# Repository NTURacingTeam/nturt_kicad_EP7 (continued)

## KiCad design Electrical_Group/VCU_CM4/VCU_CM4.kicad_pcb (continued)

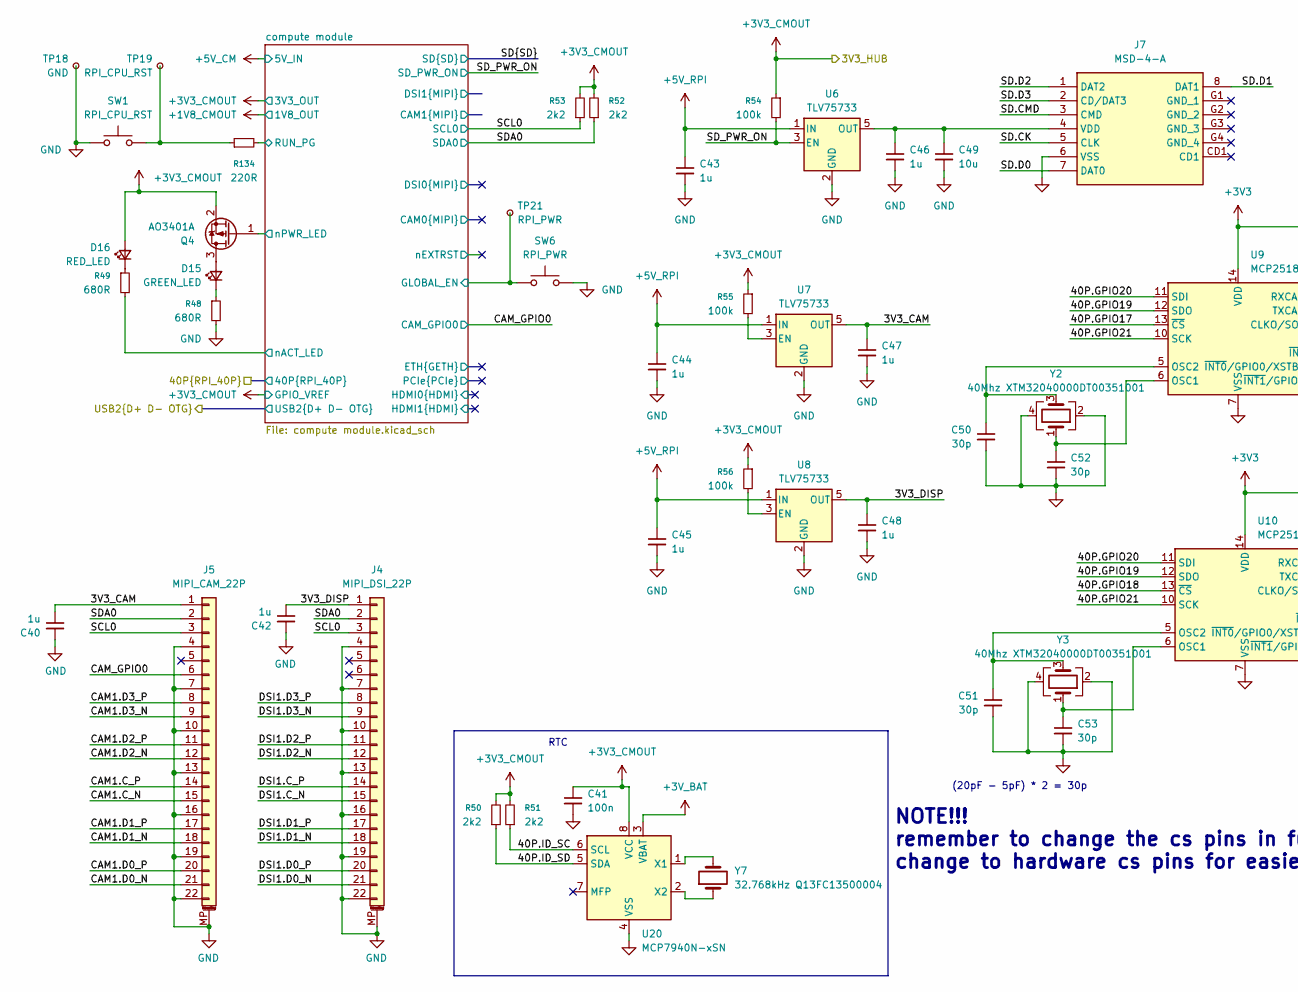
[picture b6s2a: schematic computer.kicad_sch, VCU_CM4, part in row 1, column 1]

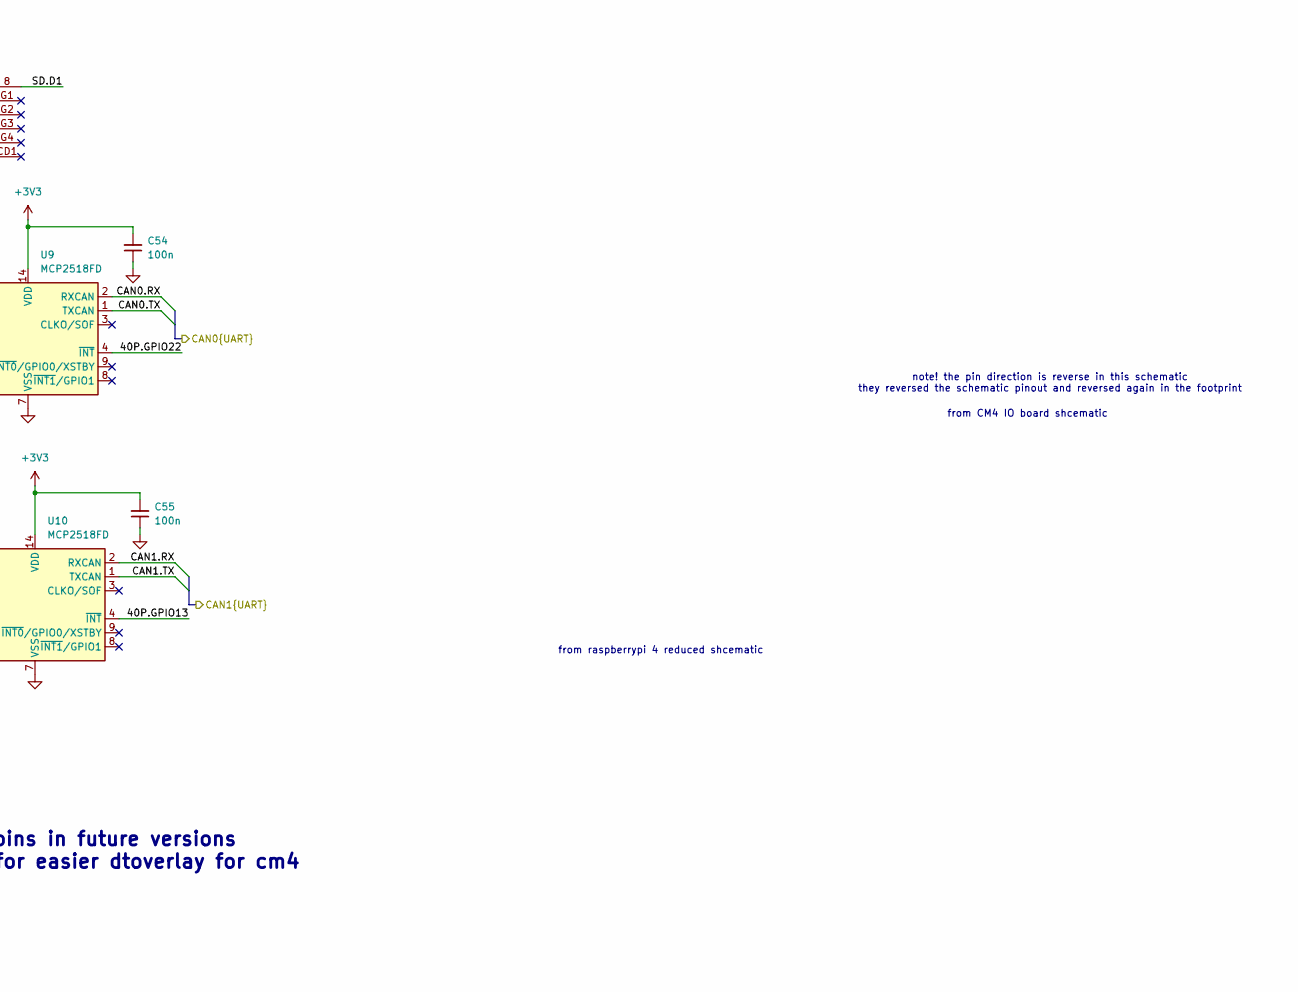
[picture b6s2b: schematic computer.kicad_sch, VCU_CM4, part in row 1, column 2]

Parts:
C40, C42, C43, C44, C45, C46, C47, C48: 1u; C_0402_1005Metric
C41: 100n; C_0603_1608Metric
C49: 10u; C_0603_1608Metric
C50, C51, C52, C53: 30p; C_0402_1005Metric
C54, C55: 100n; C_0402_1005Metric
D15: GREEN_LED; LED_0603_1608Metric
D16: RED_LED; LED_0603_1608Metric
J4: MIPI_DSI_22P; Hirose_FH12-22S-0.5SH_1x22-1MP_P0.50mm_Horizontal; Part Description 22 Position FFC, FPC Connector Contacts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
J5: MIPI_CAM_22P; Hirose_FH12-22S-0.5SH_1x22-1MP_P0.50mm_Horizontal; Part Description 22 Position FFC, FPC Connector Contacts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
J7: MSD-4-A; MSD4A; Mouser Part Number 179-MSD-4-A
Q4: AO3401A; SOT-23
R48, R49: 680R; R_0402_1005Metric
R50, R51, R52, R53: 2k2; R_0402_1005Metric
R54, R55, R56: 100k; R_0402_1005Metric
R134: 220R; R_0402_1005Metric
SW1: RPI_CPU_RST; SW_Tactile_SPST_NO_Straight_CK_PTS636Sx25SMTRLFS
SW6: RPI_PWR; SW_Tactile_SPST_NO_Straight_CK_PTS636Sx25SMTRLFS
TP18: GND; edge_pad_1.4mm_0.7mm
TP19: RPI_CPU_RST; edge_pad_1.4mm_0.7mm
TP21: RPI_PWR; edge_pad_1.4mm_0.7mm
U6, U7, U8: TLV75733; SOT-23-5
U9, U10: MCP2518FD; SOIC-14_3.9x8.7mm_P1.27mm
U20: MCP7940N-xSN; SOIC-8_3.9x4.9mm_P1.27mm
Y2, Y3: 40Mhz XTM32040000DT00351001; Crystal_SMD_3225-4Pin_3.2x2.5mm
Y7: 32.768kHz Q13FC13500004; Crystal_SMD_3215-2Pin_3.2x1.5mm

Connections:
+3V3: C54.2, C55.2, U9.14 (VDD), U10.14 (VDD); also elsewhere on the board
+3V3_CMOUT: C41.1, D16.2 (A), Q4.2 (S), R50.2, R51.2, R52.2, R53.2, R54.1, R55.1, R56.1, U20.8 (VCC); also elsewhere on the board
+3V_BAT: U20.3 (VBAT); also elsewhere on the board
+5V_CM: C43.1, C44.1, C45.1, U6.1 (IN), U7.1 (IN), U8.1 (IN); also elsewhere on the board
/RPI CAN0/CAN.RX: U9.2 (RXCAN); also elsewhere on the board
/RPI CAN0/CAN.TX: U9.1 (TXCAN); also elsewhere on the board
/RPI CAN1/CAN.RX: U10.2 (RXCAN); also elsewhere on the board
/RPI CAN1/CAN.TX: U10.1 (TXCAN); also elsewhere on the board
/computer/3V3_CAM: C40.1, C47.1, J5.1, U7.5 (OUT)
/computer/3V3_DISP: C42.1, C48.1, J4.1, U8.5 (OUT)
/computer/40P.GPIO13: U10.4 (~INT); also elsewhere on the board
/computer/40P.GPIO17: U9.13 (~CS); also elsewhere on the board
/computer/40P.GPIO18: U10.13 (~CS); also elsewhere on the board
/computer/40P.GPIO19: U9.12 (SDO), U10.12 (SDO); also elsewhere on the board
/computer/40P.GPIO20: U9.11 (SDI), U10.11 (SDI); also elsewhere on the board
/computer/40P.GPIO21: U9.10 (SCK), U10.10 (SCK); also elsewhere on the board
/computer/40P.GPIO22: U9.4 (~INT); also elsewhere on the board
/computer/40P.ID_SC: R51.1, U20.6 (SCL); also elsewhere on the board
/computer/40P.ID_SD: R50.1, U20.5 (SDA); also elsewhere on the board
/computer/CAM_GPIO0: J5.6; also elsewhere on the board
/computer/SCL0: J4.3, J5.3, R53.1; also elsewhere on the board
/computer/SD.CK: J7.5 (CLK); also elsewhere on the board
/computer/SD.CMD: J7.3 (CMD); also elsewhere on the board
/computer/SD.D0: J7.7 (DAT0); also elsewhere on the board
/computer/SD.D1: J7.8 (DAT1); also elsewhere on the board
/computer/SD.D2: J7.1 (DAT2); also elsewhere on the board
/computer/SD.D3: J7.2 (CD/DAT3); also elsewhere on the board
/computer/SDA0: J4.2, J5.2, R52.1; also elsewhere on the board
/computer/SD_PWR_ON: R54.2, U6.3 (EN); also elsewhere on the board
/computer/compute module/CAM1.C_N: J5.15; also elsewhere on the board
/computer/compute module/CAM1.C_P: J5.14; also elsewhere on the board
/computer/compute module/CAM1.D0_N: J5.21; also elsewhere on the board
/computer/compute module/CAM1.D0_P: J5.20; also elsewhere on the board
/computer/compute module/CAM1.D1_N: J5.18; also elsewhere on the board
/computer/compute module/CAM1.D1_P: J5.17; also elsewhere on the board
/computer/compute module/CAM1.D2_N: J5.12; also elsewhere on the board
/computer/compute module/CAM1.D2_P: J5.11; also elsewhere on the board
/computer/compute module/CAM1.D3_N: J5.9; also elsewhere on the board
/computer/compute module/CAM1.D3_P: J5.8; also elsewhere on the board
/computer/compute module/DSI1.C_N: J4.15; also elsewhere on the board
/computer/compute module/DSI1.C_P: J4.14; also elsewhere on the board
/computer/compute module/DSI1.D0_N: J4.21; also elsewhere on the board
/computer/compute module/DSI1.D0_P: J4.20; also elsewhere on the board
/computer/compute module/DSI1.D1_N: J4.18; also elsewhere on the board
/computer/compute module/DSI1.D1_P: J4.17; also elsewhere on the board
/computer/compute module/DSI1.D2_N: J4.12; also elsewhere on the board
/computer/compute module/DSI1.D2_P: J4.11; also elsewhere on the board
/computer/compute module/DSI1.D3_N: J4.9; also elsewhere on the board
/computer/compute module/DSI1.D3_P: J4.8; also elsewhere on the board
/computer/compute module/GLOBAL_EN: SW6.1, TP21.1; also elsewhere on the board
/computer/compute module/RUN_PG: R134.2; also elsewhere on the board
/computer/compute module/nACT_LED: R49.2; also elsewhere on the board
/computer/compute module/nPWR_LED: Q4.1 (G); also elsewhere on the board
GND: C40.2, C41.2, C42.2, C43.2, C44.2, C45.2, C46.2, C47.2, C48.2, C49.2, C50.2, C51.2, C52.2, C53.2, C54.1, C55.1, J4.4, J4.7, J4.10, J4.13, J4.16, J4.19, J4.22, J4.MP (MountPin), J5.4, J5.7, J5.10, J5.13, J5.16, J5.19, J5.22, J5.MP (MountPin), J7.6 (VSS), R48.2, SW1.2, SW6.2, TP18.1, U6.2 (GND), U7.2 (GND), U8.2 (GND), U9.7 (VSS), U10.7 (VSS), U20.4 (VSS), Y2.2, Y2.4, Y3.2, Y3.4; also elsewhere on the board
unnamed: D15.2 (A), Q4.3 (D)
unnamed: D15.1 (K), R48.1
unnamed: D16.1 (K), R49.1
unnamed: C46.1, C49.1, J7.4 (VDD), U6.5 (OUT)
unnamed: R134.1, SW1.1, TP19.1
unnamed: R55.2, U7.3 (EN)
unnamed: R56.2, U8.3 (EN)
unnamed: C52.1, U9.6 (OSC1), Y2.1
unnamed: C50.1, U9.5 (OSC2), Y2.3
unnamed: C53.1, U10.6 (OSC1), Y3.1
unnamed: C51.1, U10.5 (OSC2), Y3.3
unnamed: U20.1 (X1), Y7.2
unnamed: U20.2 (X2), Y7.1

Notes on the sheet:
from raspberrypi 4 reduced shcematic
note! the pin direction is reverse in this schematic they reversed the schematic pinout and reversed again in the footprint
(20pF - 5pF) * 2 = 30p
NOTE!!! remember to change the cs pins in future versions change to hardware cs pins for easier dtoverlay for cm4
from CM4 IO board shcematic
RTC

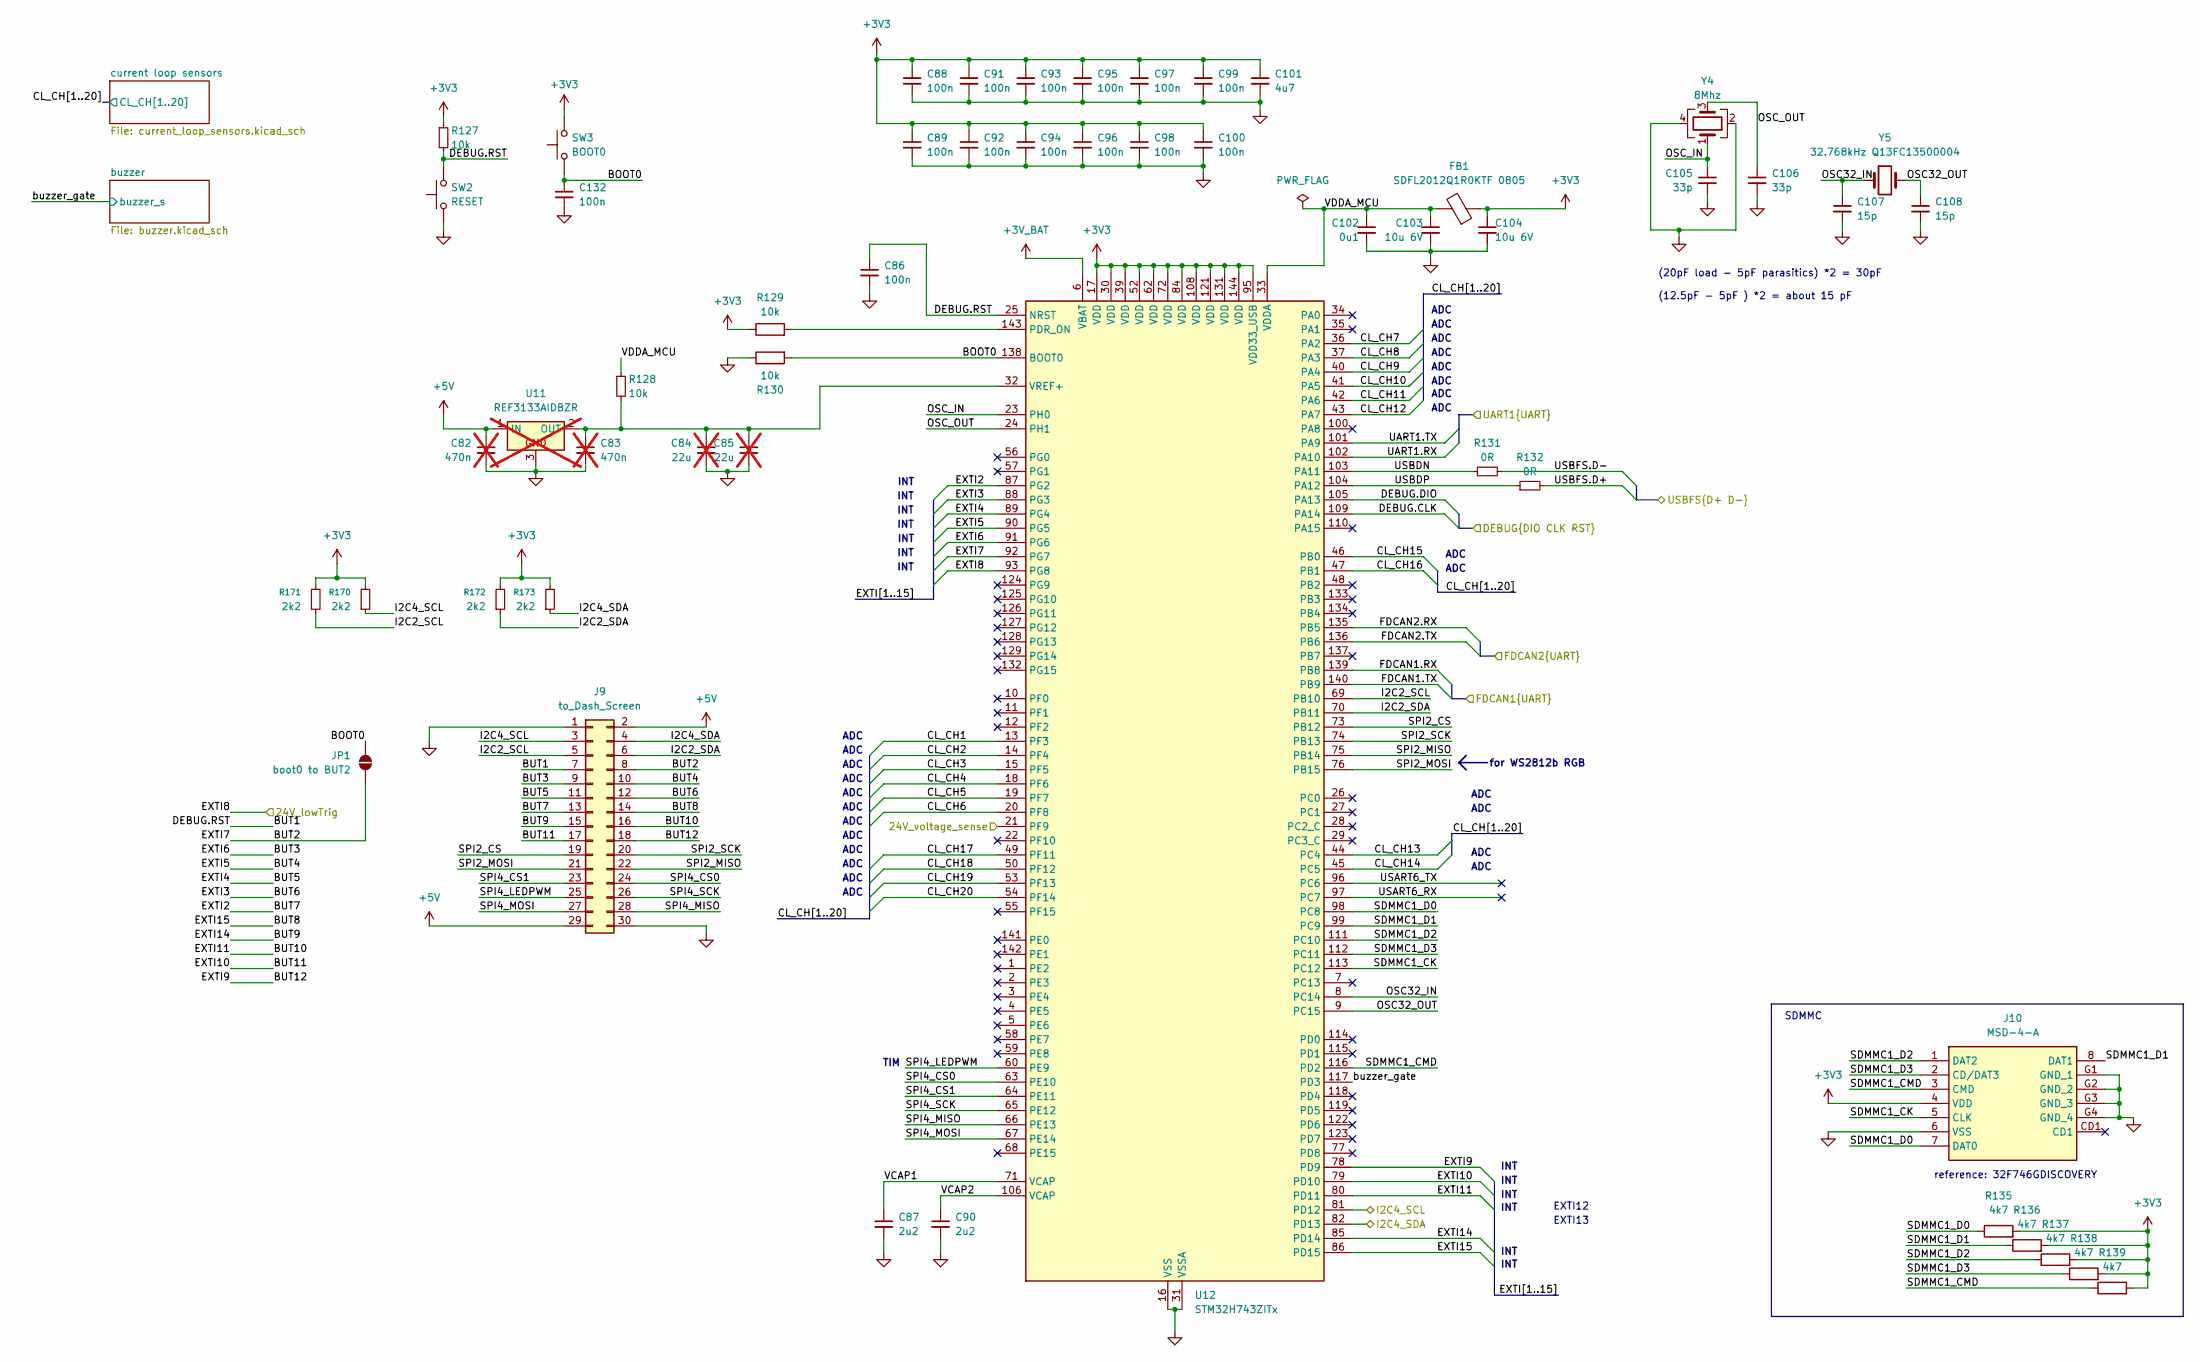
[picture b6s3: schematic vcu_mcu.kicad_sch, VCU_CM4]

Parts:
C82, C83: 470n; C_0603_1608Metric; not fitted
C84, C85: 22u; C_0805_2012Metric; not fitted
C86, C88, C89, C91, C92, C93, C94, C95, C96, C97, C98, C99, C100, C132: 100n; C_0402_1005Metric
C87, C90: 2u2; C_0402_1005Metric
C101: 4u7; C_0402_1005Metric
C102: 0u1; C_0402_1005Metric
C103, C104: 10u 6V; C_0402_1005Metric
C105, C106: 33p; C_0402_1005Metric
C107, C108: 15p; C_0402_1005Metric
FB1: SDFL2012Q1R0KTF 0805; L_0805_2012Metric
J9: to_Dash_Screen; PinHeader_2x15_P2.00mm_Vertical_SMD
J10: MSD-4-A; MSD4A; Mouser Part Number 179-MSD-4-A
JP1: boot0 to BUT2; SolderJumper-2_P1.3mm_Open_RoundedPad1.0x1.5mm
R127, R129, R130: 10k; R_0402_1005Metric
R128: 10k; R_0603_1608Metric_Pad0.98x0.95mm_HandSolder
R131, R132: 0R; R_0402_1005Metric_Pad0.72x0.64mm_HandSolder
R135, R136, R137, R138, R139: 4k7; R_0402_1005Metric
R170, R171, R172, R173: 2k2; R_0402_1005Metric
SW2: RESET; SW_Tactile_SPST_NO_Straight_CK_PTS636Sx25SMTRLFS
SW3: BOOT0; SW_Tactile_SPST_NO_Straight_CK_PTS636Sx25SMTRLFS
U11: REF3133AIDBZR; SOT-23; not fitted
U12: STM32H743ZITx; LQFP-144_20x20mm_P0.5mm
Y4: 8Mhz; Crystal_SMD_3225-4Pin_3.2x2.5mm
Y5: 32.768kHz Q13FC13500004; Crystal_SMD_3215-2Pin_3.2x1.5mm

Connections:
+3V3: C88.1, C89.1, C91.1, C92.1, C93.1, C94.1, C95.1, C96.1, C97.1, C98.1, C99.1, C100.1, C101.1, C104.1, FB1.1, J10.4 (VDD), R127.1, R129.1, R135.2, R136.2, R137.2, R138.2, R139.2, R170.2, R171.2, R172.2, R173.2, SW3.2, U12.17 (VDD), U12.30 (VDD), U12.39 (VDD), U12.52 (VDD), U12.62 (VDD), U12.72 (VDD), U12.84 (VDD), U12.95 (VDD33_USB), U12.108 (VDD), U12.121 (VDD), U12.131 (VDD), U12.144 (VDD); also elsewhere on the board
+3V_BAT: U12.6 (VBAT); also elsewhere on the board
+5V: C82.1, J9.2, J9.29, U11.1 (IN); also elsewhere on the board
/24V_lowTrig: U12.93 (PG8); also elsewhere on the board
/DFP0.D+: R132.2; also elsewhere on the board
/DFP0.D-: R131.2; also elsewhere on the board
/STM32 CAN1/CAN.RX: U12.139 (PB8); also elsewhere on the board
/STM32 CAN1/CAN.TX: U12.140 (PB9); also elsewhere on the board
/STM32 CAN2/CAN.RX: U12.135 (PB5); also elsewhere on the board
/STM32 CAN2/CAN.TX: U12.136 (PB6); also elsewhere on the board
/power/24V_SENSE: U12.21 (PF9); also elsewhere on the board
/stlink/DEBUG.CLK: U12.109 (PA14); also elsewhere on the board
/stlink/DEBUG.DIO: U12.105 (PA13); also elsewhere on the board
/stlink/DEBUG.RST: C86.1, J9.7, R127.2, SW2.2, U12.25 (NRST); also elsewhere on the board
/stlink/VCP_MCU_UART.RX: U12.102 (PA10); also elsewhere on the board
/stlink/VCP_MCU_UART.TX: U12.101 (PA9); also elsewhere on the board
/vcu mcu/BOOT0: C132.1, JP1.2 (B), R130.2, SW3.1, U12.138 (BOOT0)
/vcu mcu/CL_CH1: U12.13 (PF3); also elsewhere on the board
/vcu mcu/CL_CH2: U12.14 (PF4); also elsewhere on the board
/vcu mcu/CL_CH3: U12.15 (PF5); also elsewhere on the board
/vcu mcu/CL_CH4: U12.18 (PF6); also elsewhere on the board
/vcu mcu/CL_CH5: U12.19 (PF7); also elsewhere on the board
/vcu mcu/CL_CH6: U12.20 (PF8); also elsewhere on the board
/vcu mcu/CL_CH7: U12.36 (PA2); also elsewhere on the board
/vcu mcu/CL_CH8: U12.37 (PA3); also elsewhere on the board
/vcu mcu/CL_CH9: U12.40 (PA4); also elsewhere on the board
/vcu mcu/CL_CH10: U12.41 (PA5); also elsewhere on the board
/vcu mcu/CL_CH11: U12.42 (PA6); also elsewhere on the board
/vcu mcu/CL_CH12: U12.43 (PA7); also elsewhere on the board
/vcu mcu/CL_CH13: U12.44 (PC4); also elsewhere on the board
/vcu mcu/CL_CH14: U12.45 (PC5); also elsewhere on the board
/vcu mcu/CL_CH15: U12.46 (PB0); also elsewhere on the board
/vcu mcu/CL_CH16: U12.47 (PB1); also elsewhere on the board
/vcu mcu/CL_CH17: U12.49 (PF11); also elsewhere on the board
/vcu mcu/CL_CH18: U12.50 (PF12); also elsewhere on the board
/vcu mcu/CL_CH19: U12.53 (PF13); also elsewhere on the board
/vcu mcu/CL_CH20: U12.54 (PF14); also elsewhere on the board
/vcu mcu/EXTI2: J9.13, U12.87 (PG2)
/vcu mcu/EXTI3: J9.12, U12.88 (PG3)
/vcu mcu/EXTI4: J9.11, U12.89 (PG4)
/vcu mcu/EXTI5: J9.10, U12.90 (PG5)
/vcu mcu/EXTI6: J9.9, U12.91 (PG6)
/vcu mcu/EXTI7: J9.8, JP1.1 (A), U12.92 (PG7)
/vcu mcu/EXTI9: J9.18, U12.78 (PD9)
/vcu mcu/EXTI10: J9.17, U12.79 (PD10)
/vcu mcu/EXTI11: J9.16, U12.80 (PD11)
/vcu mcu/EXTI14: J9.15, U12.85 (PD14)
/vcu mcu/EXTI15: J9.14, U12.86 (PD15)
/vcu mcu/I2C2_SCL: J9.5, R171.1, U12.69 (PB10)
/vcu mcu/I2C2_SDA: J9.6, R172.1, U12.70 (PB11)
/vcu mcu/I2C4_SCL: J9.3, R170.1, U12.81 (PD12); also elsewhere on the board
/vcu mcu/I2C4_SDA: J9.4, R173.1, U12.82 (PD13); also elsewhere on the board
/vcu mcu/OSC32_IN: C107.1, U12.8 (PC14), Y5.1
/vcu mcu/OSC32_OUT: C108.1, U12.9 (PC15), Y5.2
/vcu mcu/OSC_IN: C105.1, U12.23 (PH0), Y4.1
/vcu mcu/OSC_OUT: C106.1, U12.24 (PH1), Y4.3
/vcu mcu/SDMMC1_CK: J10.5 (CLK), U12.113 (PC12)
/vcu mcu/SDMMC1_CMD: J10.3 (CMD), R139.1, U12.116 (PD2)
/vcu mcu/SDMMC1_D0: J10.7 (DAT0), R135.1, U12.98 (PC8)
/vcu mcu/SDMMC1_D1: J10.8 (DAT1), R136.1, U12.99 (PC9)
/vcu mcu/SDMMC1_D2: J10.1 (DAT2), R137.1, U12.111 (PC10)
/vcu mcu/SDMMC1_D3: J10.2 (CD/DAT3), R138.1, U12.112 (PC11)
/vcu mcu/SPI2_CS: J9.19, U12.73 (PB12)
/vcu mcu/SPI2_MISO: J9.22, U12.75 (PB14)
/vcu mcu/SPI2_MOSI: J9.21, U12.76 (PB15)
/vcu mcu/SPI2_SCK: J9.20, U12.74 (PB13)
/vcu mcu/SPI4_CS0: J9.24, U12.63 (PE10)
/vcu mcu/SPI4_CS1: J9.23, U12.64 (PE11)
/vcu mcu/SPI4_LEDPWM: J9.25, U12.60 (PE9)
/vcu mcu/SPI4_MISO: J9.28, U12.66 (PE13)
/vcu mcu/SPI4_MOSI: J9.27, U12.67 (PE14)
/vcu mcu/SPI4_SCK: J9.26, U12.65 (PE12)
/vcu mcu/USART6_RX: U12.97 (PC7)
/vcu mcu/USART6_TX: U12.96 (PC6)
/vcu mcu/USBDN: R131.1, U12.103 (PA11)
/vcu mcu/USBDP: R132.1, U12.104 (PA12)
/vcu mcu/VCAP1: C87.1, U12.71 (VCAP)
/vcu mcu/VCAP2: C90.1, U12.106 (VCAP)
/vcu mcu/VDDA_MCU: C102.1, C103.1, FB1.2, R128.1, U12.33 (VDDA)
/vcu mcu/buzzer_gate: U12.117 (PD3); also elsewhere on the board
GND: C82.2, C83.2, C84.2, C85.2, C86.2, C87.2, C88.2, C89.2, C90.2, C91.2, C92.2, C93.2, C94.2, C95.2, C96.2, C97.2, C98.2, C99.2, C100.2, C101.2, C102.2, C103.2, C104.2, C105.2, C106.2, C107.2, C108.2, C132.2, J9.1, J9.30, J10.6 (VSS), J10.G1 (GND_1), J10.G2 (GND_2), J10.G3 (GND_3), J10.G4 (GND_4), R130.1, SW2.1, U11.3, U12.16 (VSS), U12.31 (VSSA), U12.38 (VSS), U12.51 (VSS), U12.61 (VSS), U12.83 (VSS), U12.94 (VSS), U12.107 (VSS), U12.120 (VSS), U12.130 (VSS), Y4.2, Y4.4; also elsewhere on the board
unnamed: C83.1, C84.1, C85.1, R128.2, U11.2 (OUT), U12.32 (VREF+)
unnamed: R129.2, U12.143 (PDR_ON)

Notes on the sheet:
ADC
for WS2812b RGB
SDMMC
INT
EXTI13
EXTI12
(20pF load - 5pF parasitics) *2 = 30pF (12.5pF - 5pF ) *2 = about 15 pF
reference: 32F746GDISCOVERY
TIM

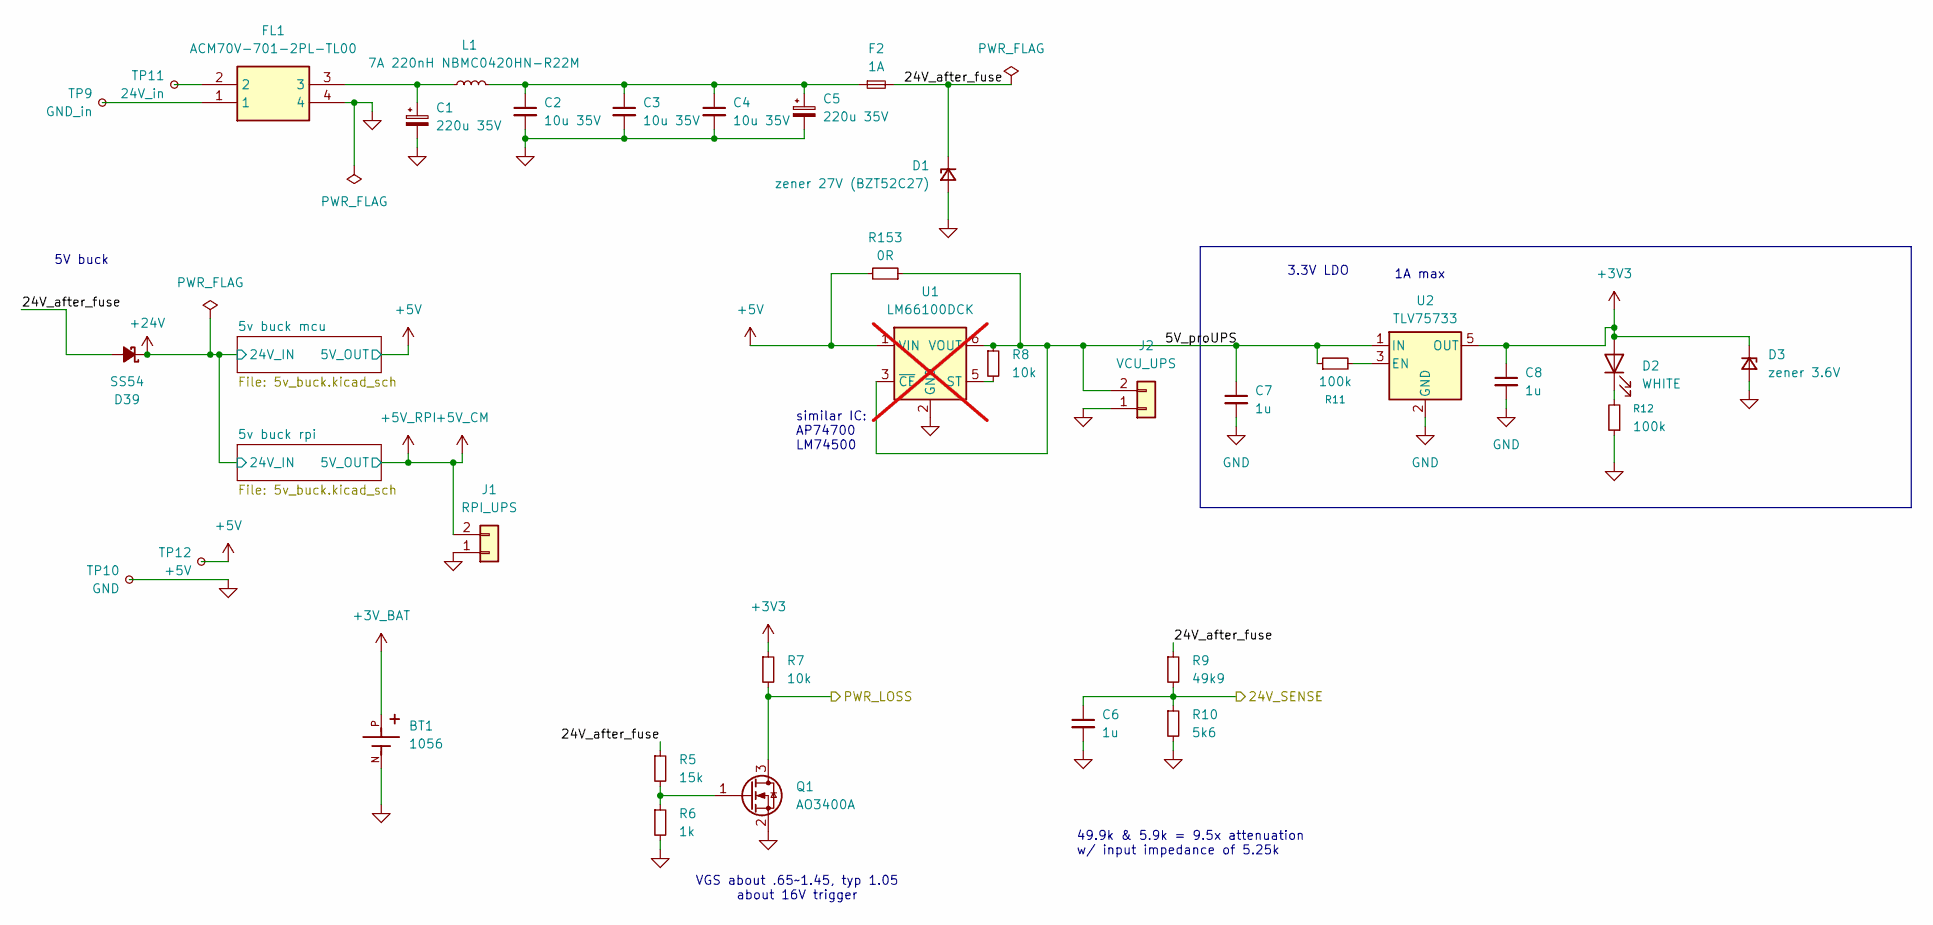
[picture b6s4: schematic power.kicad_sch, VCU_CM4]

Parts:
BT1: 1056; BAT_1056; PARTREV D
C1, C5: 220u 35V; CP_Elec_6.3x5.2
C2, C3, C4: 10u 35V; C_1206_3216Metric
C6, C7, C8: 1u; C_0402_1005Metric
D1: zener 27V (BZT52C27); D_SOD-123
D2: WHITE; LED_0603_1608Metric
D3: zener 3.6V; D_SOD-123
D39: SS54; D_SMA
F2: 1A; Fuse_1206_3216Metric
FL1: ACM70V-701-2PL-TL00; Common_Mode_Choke_4A_ACM70V7012PLTL00; Mouser Part Number 810-ACM70V7012PLTL00
J1: RPI_UPS; PinHeader_1x02_P2.00mm_Horizontal
J2: VCU_UPS; PinHeader_1x02_P2.00mm_Horizontal
L1: 7A 220nH NBMC0420HN-R22M; L_Ferrocore_DLG-0403
Q1: AO3400A; SOT-23
R5: 15k; R_0402_1005Metric
R6: 1k; R_0402_1005Metric
R7, R8: 10k; R_0402_1005Metric
R9: 49k9; R_0402_1005Metric
R10: 5k6; R_0402_1005Metric
R11, R12: 100k; R_0402_1005Metric
R153: 0R; R_0603_1608Metric
TP9: GND_in; edge_pad_1.4mm_0.7mm
TP10: GND; edge_pad_1.4mm_0.7mm
TP11: 24V_in; edge_pad_1.4mm_0.7mm
TP12: +5V; edge_pad_1.4mm_0.7mm
U1: LM66100DCK; SOT-363_SC-70-6; not fitted
U2: TLV75733; SOT-23-5

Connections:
+3V3: C8.1, D2.2 (A), D3.1 (K), R7.1, U2.5 (OUT); also elsewhere on the board
+3V_BAT: BT1.P; also elsewhere on the board
+5V: R153.2, TP12.1, U1.1 (VIN); also elsewhere on the board
+5V_CM: J1.2; also elsewhere on the board
+24V: D39.1 (K); also elsewhere on the board
/24V_lowTrig: Q1.3 (D), R7.2; also elsewhere on the board
/power/5V_proUPS: C7.1, J2.2, R8.1, R11.1, R153.1, U1.3 (~CE), U1.6 (VOUT), U2.1 (IN)
/power/24V_SENSE: C6.1, R9.2, R10.1; also elsewhere on the board
/power/24V_after_fuse: D1.1 (K), D39.2 (A), F2.2, R5.1, R9.1
GND: BT1.N, C1.2, C2.2, C3.2, C4.2, C5.2, C6.2, C7.2, C8.2, D1.2 (A), D3.2 (A), FL1.4, J1.1, J2.1, Q1.2 (S), R6.2, R10.2, R12.1, TP10.1, U1.2 (GND), U2.2 (GND); also elsewhere on the board
unnamed: C1.1, FL1.3, L1.1
unnamed: C2.1, C3.1, C4.1, C5.1, F2.1, L1.2
unnamed: D2.1 (K), R12.2
unnamed: FL1.1, TP9.1
unnamed: FL1.2, TP11.1
unnamed: Q1.1 (G), R5.2, R6.1
unnamed: R8.2, U1.5 (ST)
unnamed: R11.2, U2.3 (EN)

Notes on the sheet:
similar IC: AP74700 LM74500
5V buck
49.9k & 5.9k = 9.5x attenuation w/ input impedance of 5.25k
1A max
VGS about .65~1.45, typ 1.05 about 16V trigger
3.3V LDO

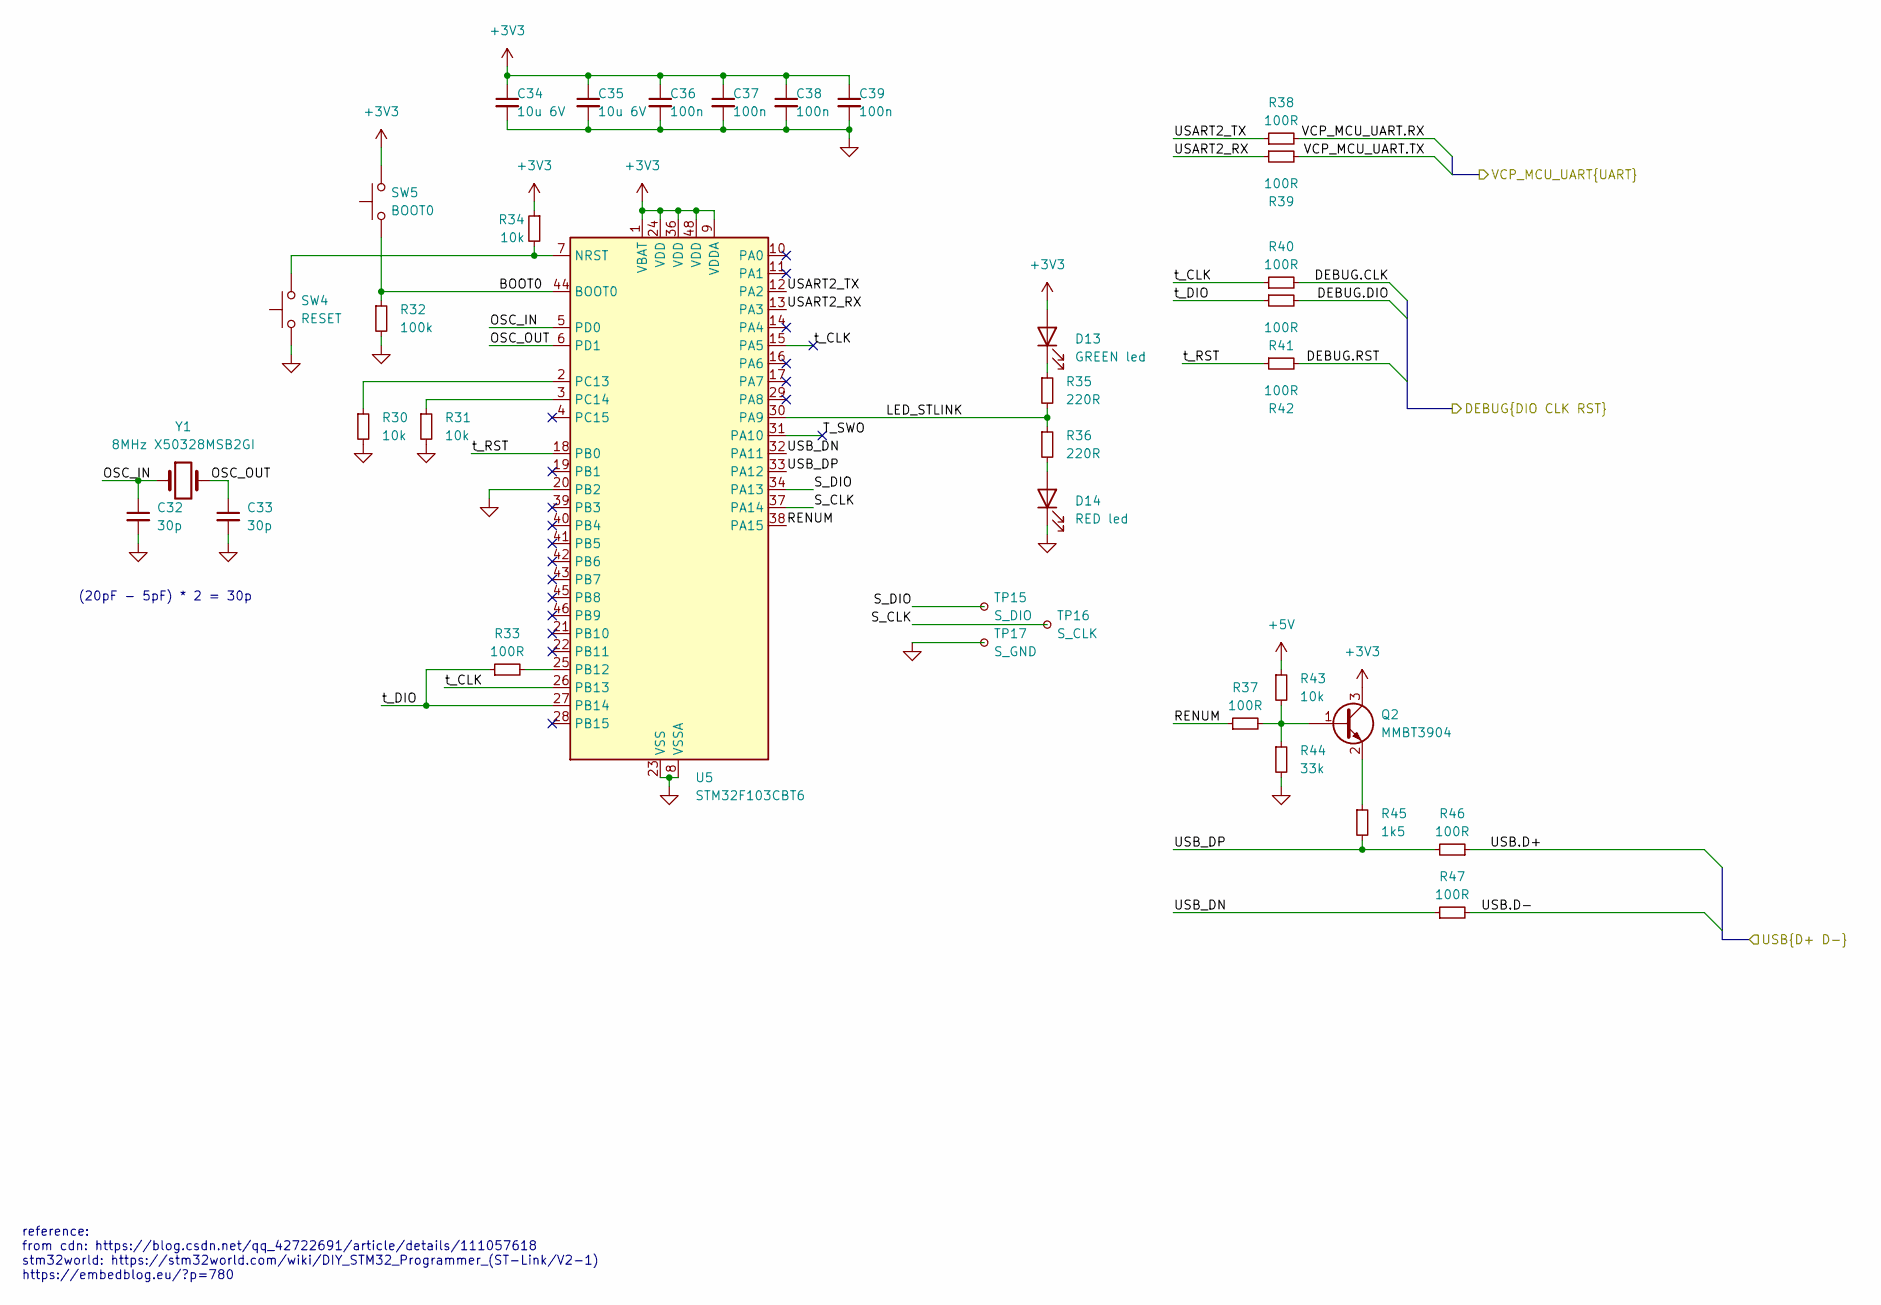
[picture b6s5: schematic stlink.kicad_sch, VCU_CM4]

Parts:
C32, C33: 30p; C_0402_1005Metric
C34, C35: 10u 6V; C_0402_1005Metric
C36, C37, C38, C39: 100n; C_0402_1005Metric
D13: GREEN led; LED_0603_1608Metric
D14: RED led; LED_0603_1608Metric
Q2: MMBT3904; SOT-23
R30, R31, R34, R43: 10k; R_0402_1005Metric
R32: 100k; R_0402_1005Metric
R33, R37: 100R; R_0402_1005Metric
R35, R36: 220R; R_0402_1005Metric
R38, R39, R40, R41, R42: 100R; R_0603_1608Metric_Pad0.98x0.95mm_HandSolder
R44: 33k; R_0402_1005Metric
R45: 1k5; R_0402_1005Metric
R46, R47: 100R; R_0402_1005Metric_Pad0.72x0.64mm_HandSolder
SW4: RESET; SW_Tactile_SPST_NO_Straight_CK_PTS636Sx25SMTRLFS
SW5: BOOT0; SW_Tactile_SPST_NO_Straight_CK_PTS636Sx25SMTRLFS
TP15: S_DIO; TestPoint_Pad_D1.0mm
TP16: S_CLK; TestPoint_Pad_D1.0mm
TP17: S_GND; TestPoint_Pad_D1.0mm
U5: STM32F103CBT6; LQFP-48_7x7mm_P0.5mm
Y1: 8MHz X50328MSB2GI; Crystal_SMD_5032-2Pin_5.0x3.2mm

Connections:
+3V3: C34.1, C35.1, C36.1, C37.1, C38.1, C39.1, D13.2 (A), Q2.3 (C), R34.1, SW5.2, U5.1 (VBAT), U5.9 (VDDA), U5.24 (VDD), U5.36 (VDD), U5.48 (VDD); also elsewhere on the board
+5V: R43.1; also elsewhere on the board
/DFP2.D+: R46.1; also elsewhere on the board
/DFP2.D-: R47.2; also elsewhere on the board
/stlink/BOOT0: R32.1, SW5.1, U5.44 (BOOT0)
/stlink/DEBUG.CLK: R40.2; also elsewhere on the board
/stlink/DEBUG.DIO: R41.2; also elsewhere on the board
/stlink/DEBUG.RST: R42.2; also elsewhere on the board
/stlink/LED_STLINK: R35.2, R36.1, U5.30 (PA9)
/stlink/OSC_IN: C32.1, U5.5 (PD0), Y1.1
/stlink/OSC_OUT: C33.1, U5.6 (PD1), Y1.2
/stlink/RENUM: R37.1, U5.38 (PA15)
/stlink/S_CLK: TP16.1, U5.37 (PA14)
/stlink/S_DIO: TP15.1, U5.34 (PA13)
/stlink/T_SWO: U5.31 (PA10)
/stlink/USART2_RX: R39.1, U5.13 (PA3)
/stlink/USART2_TX: R38.1, U5.12 (PA2)
/stlink/USB_DN: R47.1, U5.32 (PA11)
/stlink/USB_DP: R45.2, R46.2, U5.33 (PA12)
/stlink/VCP_MCU_UART.RX: R38.2; also elsewhere on the board
/stlink/VCP_MCU_UART.TX: R39.2; also elsewhere on the board
/stlink/t_CLK: R40.1, U5.15 (PA5), U5.26 (PB13)
/stlink/t_DIO: R33.1, R41.1, U5.27 (PB14)
/stlink/t_RST: R42.1, U5.18 (PB0)
GND: C32.2, C33.2, C34.2, C35.2, C36.2, C37.2, C38.2, C39.2, D14.1 (K), R30.2, R31.2, R32.2, R44.2, SW4.1, TP17.1, U5.8 (VSSA), U5.20 (PB2), U5.23 (VSS), U5.35 (VSS), U5.47 (VSS); also elsewhere on the board
unnamed: D13.1 (K), R35.1
unnamed: D14.2 (A), R36.2
unnamed: Q2.1 (B), R37.2, R43.2, R44.1
unnamed: Q2.2 (E), R45.1
unnamed: R34.2, SW4.2, U5.7 (NRST)
unnamed: R33.2, U5.25 (PB12)
unnamed: R30.1, U5.2 (PC13)
unnamed: R31.1, U5.3 (PC14)

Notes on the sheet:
(20pF - 5pF) * 2 = 30p
reference: from cdn: https://blog.csdn.net/qq_42722691/article/details/111057618 stm32world: https://stm32world.com/wiki/DIY_STM32_Programmer_(ST-Link/V2-1) https://embedblog.eu/?p=780

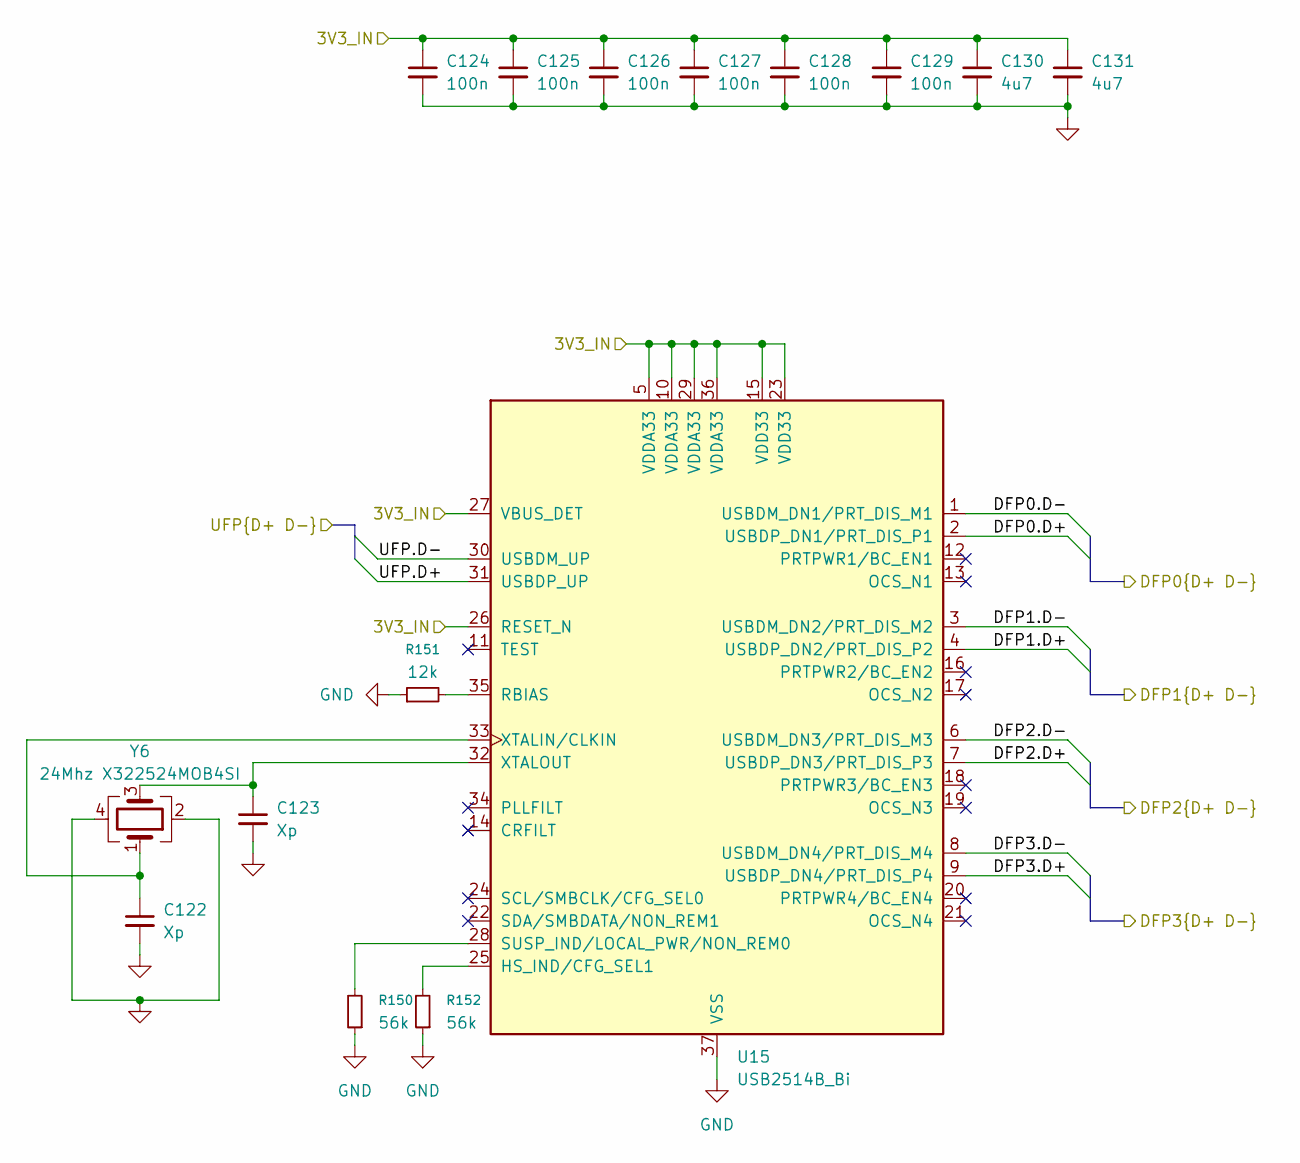
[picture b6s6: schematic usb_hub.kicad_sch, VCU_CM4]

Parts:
C122, C123: Xp; C_0402_1005Metric
C124, C125, C126, C127, C128, C129: 100n; C_0402_1005Metric
C130, C131: 4u7; C_0402_1005Metric
R150, R152: 56k; R_0402_1005Metric
R151: 12k; R_0402_1005Metric
U15: USB2514B_Bi; QFN-36-1EP_6x6mm_P0.5mm_EP3.7x3.7mm
Y6: 24Mhz X322524MOB4SI; Crystal_SMD_3225-4Pin_3.2x2.5mm

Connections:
+3V3_CMOUT: C124.1, C125.1, C126.1, C127.1, C128.1, C129.1, C130.1, C131.1, U15.5 (VDDA33), U15.10 (VDDA33), U15.15 (VDD33), U15.23 (VDD33), U15.26 (RESET_N), U15.27 (VBUS_DET), U15.29 (VDDA33), U15.36 (VDDA33); also elsewhere on the board
/DFP0.D+: U15.2 (USBDP_DN1/PRT_DIS_P1); also elsewhere on the board
/DFP0.D-: U15.1 (USBDM_DN1/PRT_DIS_M1); also elsewhere on the board
/DFP1.D+: U15.4 (USBDP_DN2/PRT_DIS_P2)
/DFP1.D-: U15.3 (USBDM_DN2/PRT_DIS_M2)
/DFP2.D+: U15.7 (USBDP_DN3/PRT_DIS_P3); also elsewhere on the board
/DFP2.D-: U15.6 (USBDM_DN3/PRT_DIS_M3); also elsewhere on the board
/DFP3.D+: U15.9 (USBDP_DN4/PRT_DIS_P4); also elsewhere on the board
/DFP3.D-: U15.8 (USBDM_DN4/PRT_DIS_M4); also elsewhere on the board
/usb hub/UFP.D+: U15.31 (USBDP_UP); also elsewhere on the board
/usb hub/UFP.D-: U15.30 (USBDM_UP); also elsewhere on the board
GND: C122.2, C123.2, C124.2, C125.2, C126.2, C127.2, C128.2, C129.2, C130.2, C131.2, R150.1, R151.1, R152.1, U15.37 (VSS), Y6.2, Y6.4; also elsewhere on the board
unnamed: R152.2, U15.25 (HS_IND/CFG_SEL1)
unnamed: R151.2, U15.35 (RBIAS)
unnamed: R150.2, U15.28 (SUSP_IND/LOCAL_PWR/NON_REM0)
unnamed: C122.1, U15.33 (XTALIN/CLKIN), Y6.1
unnamed: C123.1, U15.32 (XTALOUT), Y6.3
